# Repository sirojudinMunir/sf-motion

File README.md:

# SF-Motion

**Open-source BLDC/PMSM motor control platform based on STM32 and Field-Oriented Control (FOC).**

The project includes:

- FOC firmware
- Custom motor driver hardware
- KiCad schematic and PCB design
- Gerber and BOM files
- Python communication and control tools
- PyQt/PyQtGraph GUI for motor monitoring and testing

> ⚠️ This project is under active development. Hardware and firmware may change between versions.

## Hardware Prerequisites

You will need:
- FOC Driver Board
- ST-Link programmer/debugger with 3-pin Molex pico-blade P1.25mm connector
- DC power supply
- BLDC/PMSM motor
- diametrical magnet
- USB type-C cable
- power cable with XT-30 female connector

The hardware design is available in:
```
Hardware/
├── production/        # Gerber manufacturing files
├── .kicad_sch         # Schematic
├── .kicad_pcb         # PCB design
└── ...
```

## Software Prerequisites

### 1. STM32CubeMX

Used to configure the STM32 peripherals and generate the initial project configuration.

Download: https://www.st.com/en/development-tools/stm32cubemx.html

### 2. Visual Studio Code

Used as the main development environment.

Download: https://code.visualstudio.com/

### 3. PlatformIO

PlatformIO is used to build and upload the firmware.

Install PlatformIO through the VS Code extension:
1. Open VS Code.
2. Open Extensions.
3. Search for PlatformIO IDE.
4. Install the extension.
5. Restart VS Code if required.

Verify the installation:
``` bash
pio --version
```

If `pio` is not recognized in the terminal, use the PlatformIO terminal inside VS Code or add the PlatformIO CLI directory to your system PATH.

### 4. Python

Python is required for the communication tools and GUI.

Recommended version:
```text
Python 3.10+
```

Download: https://www.python.org/downloads/

Check the installation:
``` bash
python --version
```

Create a virtual environment (recommended):
``` bash
python -m venv .venv
```

Activate it on Windows:
``` bash
.venv\Scripts\activate
```

Activate it on Linux/macOS:
``` bash
source .venv/bin/activate
```

Install the required packages:
``` bash
pip install numpy pyserial PyQt5 pyqtgraph
```

## Getting Started

Clone the repository using Git:
``` bash
git clone https://github.com/sirojudinMunir/sf-motion.git
```

Enter the project directory:
``` bash
cd SF-Motion
```

## Building the Firmware

Open the project in VS Code with PlatformIO installed.

Build the firmware:
``` bash
pio run
```

If the build is successful, the firmware binary will be generated by PlatformIO.

## Upload Firmware

Connect the ST-Link to the FOC Driver board using the 3-pin PicoBlade connector.

The board can be powered from a **6–24 V external power supply**. For the initial test, it is recommended to use **USB Type-C** as the power source if applicable.

Upload the firmware:
``` bash
pio run -t upload
```

You can also use the Upload button in the PlatformIO interface in VS Code.

## For the first test

After uploading the firmware, follow these steps:

1. Make sure the D3 LED is blinking after the firmware starts.
2. Connect the BLDC/PMSM motor wires to the FOC Driver board. Make sure the diametrical magnet is securely mounted on the motor shaft and properly aligned with the magnetic encoder on the FOC Driver board. The board should be positioned directly beneath the magnet.
3. If you are using an external power supply, set the current limit to 1 A for the initial test. This helps prevent damage if there is an unexpected issue with the board or motor.
4. Connect the USB Type-C cable to the board.
5. Run the Python motor control program:
    ```python
    python communication/motor.py
    ```
6. Select the correct COM port and click Connect.

7. Before running the motor, set the correct motor pole pairs:
    ``` python
    motor.set_pole_pairs(<your_motor_pole_pairs>)
    ```
    Replace <your_motor_pole_pairs> with the actual number of pole pairs of your motor.
8. Run the self-commissioning process:
    ``` python
    motor.self_commissioning()
    ```
    The self-commissioning process measures the motor resistance and inductance and calibrates the magnetic encoder.
    >Important: During encoder calibration, make sure the motor rotates counter-clockwise (CCW). If the motor rotates in the opposite direction, swap any two motor wires to reverse the rotation.
    Automatic motor direction detection will be implemented in a future version.
9. Save configuration
    ``` python
    motor.set_save_config()
    ```
10. Test the FOC motor modes using:
    ``` python
    motor.set_motor_mode(<mode>)
    ```
    Available modes:

    0 -> for current control mode  
    1 -> for speed control mode  
    2 -> for position control mode  
    5 -> for open-loop mode  
    6 -> for disable the motor

> ⚠️ Keep the power supply current limit low during the first test. Do not increase the voltage or current limit until the board, encoder, and motor are confirmed to be working correctly.

---

## Support SF-Motion

If you find this project useful and would like to support its development,
you can become a sponsor:

Your support helps fund hardware development, testing, documentation,
and future improvements to SF-Motion.

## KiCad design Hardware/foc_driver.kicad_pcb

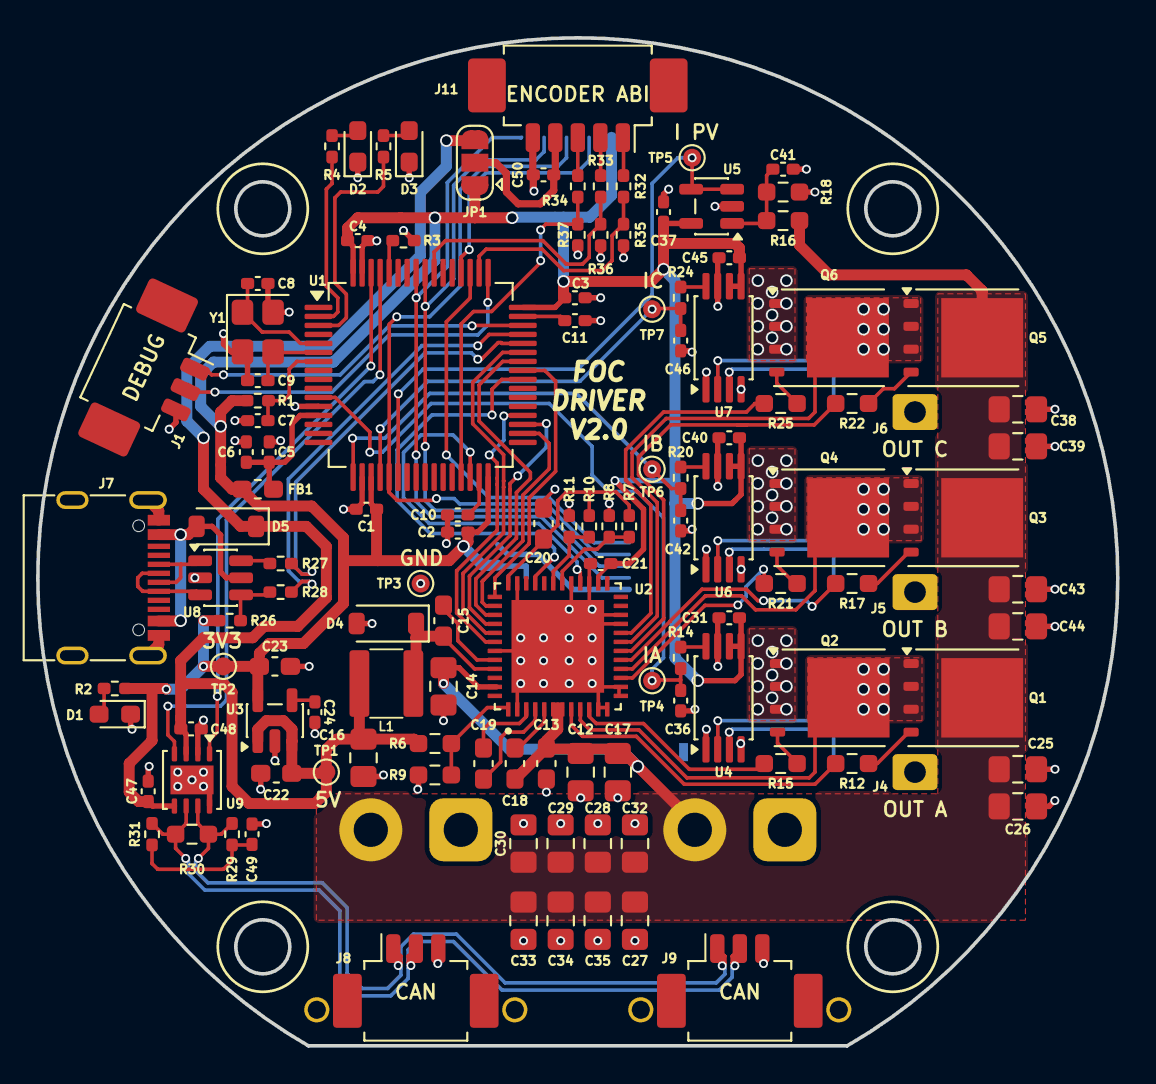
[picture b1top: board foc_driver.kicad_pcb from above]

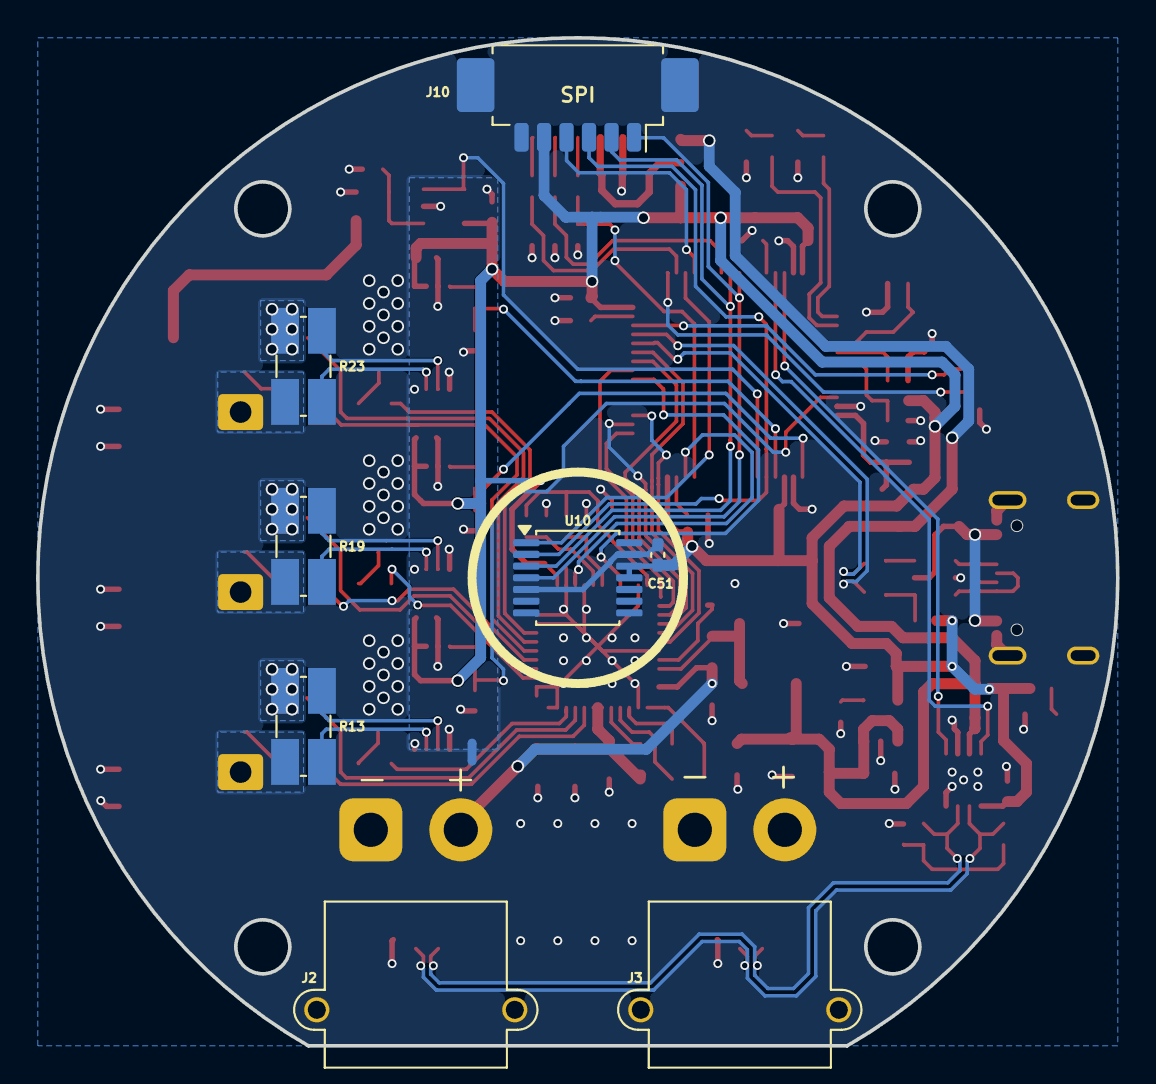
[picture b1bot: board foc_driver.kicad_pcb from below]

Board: 2 copper layers, 60.0 x 56.0 mm, 132 parts (9 on the bottom side), 93 nets.

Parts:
C1, C2, C3, C4, C5, C7, C10, C11, C21, C31, C37, C40, C41, C45, C47, C48, C49, C50, C51: 100nF; C_0402_1005Metric_Pad0.74x0.62mm_HandSolder
C6: 1uF; C_0402_1005Metric_Pad0.74x0.62mm_HandSolder
C8, C9: 33pF; C_0402_1005Metric_Pad0.74x0.62mm_HandSolder
C12, C16, C17, C25, C26, C27, C28, C29, C30, C32, C33, C34, C35, C38, C39, C43, C44: 10uF; C_0805_2012Metric_Pad1.18x1.45mm_HandSolder
C13, C15: 0.1uF; C_0603_1608Metric_Pad1.08x0.95mm_HandSolder
C14: 4.7uF; C_0805_2012Metric_Pad1.18x1.45mm_HandSolder
C18, C20, C22: 1uF; C_0603_1608Metric_Pad1.08x0.95mm_HandSolder
C19: 47nF; C_0603_1608Metric_Pad1.08x0.95mm_HandSolder
C23: 2.2uF; C_0603_1608Metric_Pad1.08x0.95mm_HandSolder
C24: 10nF; C_0402_1005Metric_Pad0.74x0.62mm_HandSolder
C36, C42, C46: 1nF; C_0402_1005Metric_Pad0.74x0.62mm_HandSolder
D1, D2: LED RED; LED_0603_1608Metric_Pad1.05x0.95mm_HandSolder
D3: LED GREEN; LED_0603_1608Metric_Pad1.05x0.95mm_HandSolder
D4, D5: MBR0530; D_SOD-123
FB1: fcm 1608-0603; L_0603_1608Metric_Pad1.05x0.95mm_HandSolder
J1, J8, J9: Conn_01x03_MountingPin; Molex_PicoBlade_53261-0371_1x03-1MP_P1.25mm_Horizontal
J2, J3: Conn_01x02; AMASS_XT30PW-M_1x02_P2.50mm_Horizontal
J4, J5, J6: Conn_01x01; SolderWire-0.25sqmm_1x01_D0.65mm_OD2mm
J7: USB_C_Receptacle_USB2.0_16P; USB_C_Receptacle_G-Switch_GT-USB-7010ASV
J10: Conn_01x06_MountingPin; Molex_PicoBlade_53261-0671_1x06-1MP_P1.25mm_Horizontal
J11: Conn_01x05_MountingPin; Molex_PicoBlade_53261-0571_1x05-1MP_P1.25mm_Horizontal
JP1: SolderJumper_3_Open; SolderJumper-3_P1.3mm_Open_RoundedPad1.0x1.5mm
L1: 22uH; L_SMD_4X4
NT1: NetTie_2; NetTie-2_SMD_Pad0.5mm
Q1, Q2, Q3, Q4, Q5, Q6: WSD30100DN56; TDSON-8-1
R1, R3: 10k; R_0402_1005Metric_Pad0.72x0.64mm_HandSolder
R2, R4, R5, R14, R20, R24, R32, R33, R34: 1k; R_0402_1005Metric_Pad0.72x0.64mm_HandSolder
R6: 18k; R_0603_1608Metric_Pad0.98x0.95mm_HandSolder
R7, R8, R10, R11: R; R_0402_1005Metric_Pad0.72x0.64mm_HandSolder
R9: 3k3; R_0603_1608Metric_Pad0.98x0.95mm_HandSolder
R12, R15, R17, R21, R22, R25: 10R; R_0603_1608Metric_Pad0.98x0.95mm_HandSolder
R13, R19, R23: 0.01R; R_Shunt_Ohmite_LVK20
R16: 39k; R_0603_1608Metric_Pad0.98x0.95mm_HandSolder
R18: 2k2; R_0603_1608Metric_Pad0.98x0.95mm_HandSolder
R26: 1k8; R_0402_1005Metric_Pad0.72x0.64mm_HandSolder
R27, R28: 100R; R_0402_1005Metric_Pad0.72x0.64mm_HandSolder
R29, R31: 30R; R_0402_1005Metric_Pad0.72x0.64mm_HandSolder
R30: 120R; R_0603_1608Metric_Pad0.98x0.95mm_HandSolder
R35, R36, R37: 2k; R_0402_1005Metric_Pad0.72x0.64mm_HandSolder
TP1, TP2, TP3, TP4, TP5, TP6, TP7: TestPoint; TestPoint_Pad_D1.0mm
U1: STM32F405RGTx; LQFP-64_10x10mm_P0.5mm
U2: DRV8323RHRGZR; QFN50P700X700X100-49N
U3: LP2985-3.3; SOT-23-5
U4, U6, U7: INA240A1PW; TSSOP-8_4.4x3mm_P0.65mm
U5: LM321; SOT-23-5
U8: USBLC6-2SC6; SOT-23-6
U9: TJA1051TK-3; HVSON-8-1EP_3x3mm_P0.65mm_EP1.6x2.4mm
U10: AS5047D; TSSOP-14_4.4x5mm_P0.65mm
Y1: 12MHz; Crystal_SMD_3225-4Pin_3.2x2.5mm

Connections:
+3V3: C1.1, C2.1, C3.1, C4.1, C21.2, C23.1, C31.1, C37.1, C40.1, C45.1, C47.2, C51.1, FB1.2, J10.5, JP1.1 (A), R1.1, R2.1, R26.1, TP2.1 (1_1), U1.19 (VDD), U1.32 (VDD), U1.48 (VDD), U1.64 (VDD), U2.26 (VREF), U3.5 (VOUT), U4.5 (V+), U4.6 (REF2), U5.5 (V+), U6.5 (V+), U6.6 (REF2), U7.5 (V+), U7.6 (REF2), U9.5 (VIO), U10.11 (VDD), U10.12 (VDD3V3)
+3V3A: C5.1, C6.1, FB1.1, U1.13 (VDDA)
+5V: C16.1, C22.1, C48.2, D5.1 (K), JP1.3 (B), L1.2, R6.1, TP1.1 (1_1), U3.1 (VIN), U3.3 (ON/~OFF), U9.3 (VCC)
/Communications/CAN_N: J8.2, J9.2, R30.2, R31.2, U9.6 (CANL)
/Communications/CAN_P: J8.1, J9.1, R29.2, R30.1, U9.7 (CANH)
/Communications/CAN_RX: U1.61 (PB8), U9.4 (RXD)
/Communications/CAN_TX: U1.62 (PB9), U9.1 (TXD)
/Communications/USB_N: R27.2, U1.44 (PA11)
/Communications/USB_P: R28.2, U1.45 (PA12)
/Communications/VBUS: D5.2 (A), J7.A4 (VBUS), J7.A9 (VBUS), J7.B4 (VBUS), J7.B9 (VBUS), U8.5 (VBUS)
/Encoders/CS0: U1.51 (PC10), U10.1 (~CS)
/Encoders/CS1: J10.4, U1.52 (PC11)
/Encoders/EXT_ENCDA: R32.1, R35.1, U1.50 (PA15)
/Encoders/EXT_ENCDB: R33.1, R36.1, U1.55 (PB3)
/Encoders/EXT_ENCDI: R34.1, R37.1, U1.29 (PB10)
/Encoders/MISO: J10.2, U1.56 (PB4), U10.3 (MISO)
/Encoders/MOSI: J10.1, U1.57 (PB5), U10.4 (MOSI)
/Encoders/SCK: J10.3, U1.21 (PA5), U10.2 (CLK)
/Gate Driver/EN_GATE: U1.40 (PC9), U2.33 (ENABLE)
/Gate Driver/FAULT: U1.30 (PB11), U2.28 (NFAULT)
/Gate Driver/GHA: R12.1, U2.8 (GHA)
/Gate Driver/GHB: R17.1, U2.17 (GHB)
/Gate Driver/GHC: R22.1, U2.18 (GHC)
/Gate Driver/GLA: R15.1, U2.10 (GLA)
/Gate Driver/GLB: R21.1, U2.15 (GLB)
/Gate Driver/GLC: R25.1, U2.20 (GLC)
/Gate Driver/IDRIVE: R7.2, R8.2, U2.30 (IDRIVE)
/Gate Driver/INH_A: U1.41 (PA8), U2.37 (INHA)
/Gate Driver/INH_B: U1.42 (PA9), U2.39 (INHB)
/Gate Driver/INH_C: U1.43 (PA10), U2.41 (INHC)
/Gate Driver/INL_A: U1.34 (PB13), U2.38 (INLA)
/Gate Driver/INL_B: U1.35 (PB14), U2.40 (INLB)
/Gate Driver/INL_C: U1.36 (PB15), U2.42 (INLC)
/Gate Driver/SHA: Q1.1 (S), Q1.2 (S), Q1.3 (S), Q2.5 (D), R13.1, U2.9 (SHA)
/Gate Driver/SHB: Q3.1 (S), Q3.2 (S), Q3.3 (S), Q4.5 (D), R19.1, U2.16 (SHB)
/Gate Driver/SHC: Q5.1 (S), Q5.2 (S), Q5.3 (S), Q6.5 (D), R23.1, U2.19 (SHC)
/Gate Driver/VDS: R10.2, R11.2, U2.31 (VDS)
/Inverter/ISENSE_A: C36.1, R14.2, TP4.1 (1_1), U1.11 (PC3)
/Inverter/ISENSE_B: C42.1, R20.2, TP6.1 (1_1), U1.17 (PA3)
/Inverter/ISENSE_C: C46.1, R24.2, TP7.1 (1_1), U1.20 (PA4)
/Inverter/OUT_A: J4.1 (Pin_1_1), R13.4
/Inverter/OUT_B: J5.1 (Pin_1_1), R19.4
/Inverter/OUT_C: J6.1 (Pin_1_1), R23.4
/Inverter/PV_SENSE: TP5.1 (1_1), U1.22 (PA6), U5.3 (-), U5.4
/MCU/BOOT0: R3.2, U1.60 (BOOT0)
/MCU/LED_G: R5.1, U1.3 (PC14)
/MCU/LED_R: R4.1, U1.2 (PC13)
/MCU/NRST: C7.1, R1.2, U1.7 (NRST)
/MCU/OSC_IN: C8.2, U1.5 (PH0), Y1.1
/MCU/OSC_OUT: C9.2, U1.6 (PH1), Y1.3
/MCU/SWCLK: J1.2, U1.49 (PA14)
/MCU/SWDIO: J1.1, U1.46 (PA13)
DVDD: C20.1, R7.1, R10.1, U2.36 (DVDD)
GND: C1.2, C2.2, C3.2, C4.2, C5.2, C6.2, C7.2, C8.1, C9.1, C10.2, C11.2, C12.2, C13.2, C14.2, C16.2, C17.2, C20.2, C21.1, C22.2, C23.2, C24.2, C25.1, C26.1, C27.1, C28.1, C29.1, C30.1, C32.1, C33.1, C34.1, C35.1, C38.1, C39.1, C41.2, C43.1, C44.1, C47.1, C48.1, C49.1, C50.1, C51.2, D1.1 (K), D2.1 (K), D3.1 (K), D4.2 (A), J1.3, J2.1, J3.1, J7.A1 (GND), J7.A12 (GND), J7.B1 (GND), J7.B12 (GND), J7.S1 (SHIELD), J8.3, J9.3, J10.6, J11.5, NT1.2, Q2.1 (S), Q2.2 (S), Q2.3 (S), Q4.1 (S), Q4.2 (S), Q4.3 (S), Q6.1 (S), Q6.2 (S), Q6.3 (S), R3.1, R8.1, R9.2, R11.1, R18.2, R35.2, R36.2, R37.2, TP3.1 (1_1), U1.12 (VSSA), U1.18 (VSS), U1.63 (VSS), U2.2 (PGND), U2.11 (SPA), U2.12 (SNA), U2.13 (SNB), U2.14 (SPB), U2.21 (SPC), U2.22 (SNC), U2.27 (DGND), U2.29 (MODE), U2.35 (AGND), U2.43 (BGND), U2.49 (EP), U3.2 (GND), U8.2 (GND), U9.2 (GND), U9.8 (S), U9.9 (GND), U10.5 (TST), U10.13 (GND), Y1.2 (G), Y1.4 (G)
GNDA: C31.2, C36.2, C37.2, C40.2, C42.2, C45.2, C46.2, NT1.1, U4.1 (GND), U4.4 (GND), U4.7 (REF1), U5.2 (V-), U6.1 (GND), U6.4 (GND), U6.7 (REF1), U7.1 (GND), U7.4 (GND), U7.7 (REF1)
unnamed: C49.2, R29.1, R31.1
unnamed: D1.2 (A), R2.2
unnamed: D2.2 (A), R4.2
unnamed: D3.2 (A), R5.2
unnamed: C15.2, D4.1 (K), L1.1, U2.45 (SW)
unnamed: J7.A6 (D+), J7.B6 (D+), U8.3 (I/O2)
unnamed: J7.A7 (D-), J7.B7 (D-), U8.1 (I/O1)
unnamed: J11.1, R32.2
unnamed: J11.2, R33.2
unnamed: J11.3, R34.2
unnamed: C50.2, J11.4, JP1.2 (C)
unnamed: Q1.4 (G), R12.2
unnamed: Q2.4 (G), R15.2
unnamed: Q3.4 (G), R17.2
unnamed: Q4.4 (G), R21.2
unnamed: Q5.4 (G), R22.2
unnamed: Q6.4 (G), R25.2
unnamed: R14.1, U4.8
unnamed: R20.1, U6.8
unnamed: R24.1, U7.8
unnamed: R26.2, R28.1, U8.4 (I/O2)
unnamed: R27.1, U8.6 (I/O1)
unnamed: C10.1, U1.31 (VCAP_1)
unnamed: C11.1, U1.47 (VCAP_2)
unnamed: C15.1, U2.44 (CB)
unnamed: C19.2, U2.4 (CPH)
unnamed: C19.1, U2.3 (CPL)
unnamed: R6.2, R9.1, U2.1 (FB)
unnamed: C18.1, U2.5 (VCP)
unnamed: C24.1, U3.4 (BP)
unnamed: R13.2, U4.2 (+)
unnamed: R13.3, U4.3 (-)
unnamed: C41.1, R16.2, R18.1, U5.1 (+)
unnamed: R19.2, U6.2 (+)
unnamed: R19.3, U6.3 (-)
unnamed: R23.2, U7.2 (+)
unnamed: R23.3, U7.3 (-)
VS: C12.1, C13.1, C14.1, C17.1, C18.2, C25.2, C26.2, C27.2, C28.2, C29.2, C30.2, C32.2, C33.2, C34.2, C35.2, C38.2, C39.2, C43.2, C44.2, J2.2, J3.2, Q1.5 (D), Q3.5 (D), Q5.5 (D), R16.1, U2.6 (VM), U2.7 (VDRAIN), U2.47 (VIN)

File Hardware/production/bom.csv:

Designator,Footprint,Quantity,Value,LCSC Part #
"C1, C10, C11, C2, C21, C3, C31, C37, C4, C40, C41, C45, C47, C48, C49, C5, C50, C51, C7",0402,19,100nF,C1525
"C12, C16, C17, C25, C26, C27, C28, C29, C30, C32, C33, C34, C35, C38, C39, C43, C44",0805,17,10uF,C22367830
"C13, C15",0603,2,0.1uF,C1591
C14,0805,1,4.7uF,C98192
"C18, C20, C22",0603,3,1uF,C5199872
C19,0603,1,47nF,C1622
C23,0603,1,2.2uF,C23630
C24,0402,1,10nF,C15195
"C36, C42, C46",0402,3,1nF,C14442
C6,0402,1,1uF,C29266
"C8, C9",0402,2,33pF,C70465
"D1, D2",0603,2,LED RED,C19171390
D3,0603,1,LED GREEN,C2986048
"D4, D5",D_SOD-123,2,MBR0530,C5204746
FB1,0603,1,fcm 1608-0603,C19330
"J1, J8, J9",Molex_PicoBlade_53261-0371_1x03-1MP_P1.25mm_Horizontal,3,Conn_01x03_MountingPin,C293630
J10,Molex_PicoBlade_53261-0671_1x06-1MP_P1.25mm_Horizontal,1,Conn_01x06_MountingPin,C17393620
J11,Molex_PicoBlade_53261-0571_1x05-1MP_P1.25mm_Horizontal,1,Conn_01x05_MountingPin,C17256390
"J2, J3",AMASS_XT30PW-M_1x02_P2.50mm_Horizontal,2,Conn_01x02,C431092
"J4, J5, J6",SolderWire-0.25sqmm_1x01_D0.65mm_OD2mm,3,Conn_01x01,
J7,USB_C_Receptacle_G-Switch_GT-USB-7010ASV,1,USB_C_Receptacle_USB2.0_16P,C2927039
L1,L_SMD_4X4,1,22uH,C6364792
"Q1, Q2, Q3, Q4, Q5, Q6",TDSON-8-1,6,WSD30100DN56,C2862136
"R1, R3",0402,2,10k,C60490
"R10, R11, R7, R8",0402,4,R,
"R12, R15, R17, R21, R22, R25",0603,6,10R,C844919
"R13, R19, R23",R_Shunt_Ohmite_LVK20,3,0.01R,C844898
"R14, R2, R20, R24, R32, R33, R34, R4, R5",0402,9,1k,C852624
R16,0603,1,39k,C163424
R18,0603,1,2k2,C125931
R26,0402,1,1k8,C163481
"R27, R28",0402,2,100R,C705627
"R29, R31",0402,2,30R,C852718
R30,0603,1,120R,C125925
"R35, R36, R37",0402,3,2k,C852711
R6,0603,1,18k,C309650
R9,0603,1,3k3,C144661
"TP1, TP2, TP3, TP4, TP5, TP6, TP7",TestPoint_Pad_D1.0mm,7,TestPoint,
U1,LQFP-64_10x10mm_P0.5mm,1,STM32F405RGTx,C15742
U10,TSSOP-14_4.4x5mm_P0.65mm,1,AS5047D,C2693743
U2,QFN50P700X700X100-49N,1,DRV8323RHRGZR,C543035
U3,SOT-23-5,1,LP2985-3.3,C95414
"U4, U6, U7",TSSOP-8_4.4x3mm_P0.65mm,3,INA240A1PW,C93965
U5,SOT-23-5,1,LM321,C5252901
U8,SOT-23-6,1,USBLC6-2SC6,C2827654
U9,HVSON-8-1EP_3x3mm_P0.65mm_EP1.6x2.4mm,1,TJA1051TK-3,C2875699
Y1,Crystal_SMD_3225-4Pin_3.2x2.5mm,1,12MHz,C9002

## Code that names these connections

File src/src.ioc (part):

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Mcu.Name=STM32F405RGTx
Mcu.Package=LQFP64
Mcu.UserName=STM32F405RGTx
PA10.Signal=S_TIM1_CH3
PA11.Mode=Device_Only
PA11.Signal=USB_OTG_FS_DM
PA12.Mode=Device_Only
PA12.Signal=USB_OTG_FS_DP
PA13.Mode=Serial_Wire
PA13.Signal=SYS_JTMS-SWDIO
PA14.Mode=Serial_Wire
PA14.Signal=SYS_JTCK-SWCLK
PA3.Signal=ADCx_IN3
PA4.Signal=ADCx_IN4
PA5.Mode=Full_Duplex_Master
PA5.Signal=SPI1_SCK
PA6.Signal=ADCx_IN6
PA8.Signal=S_TIM1_CH1
PA9.Signal=S_TIM1_CH2
PB11.GPIOParameters=GPIO_Label
PB11.GPIO_Label=NFAULT1
PB11.Signal=GPIO_Input
PB13.Mode=PWM Generation1 CH1 CH1N
PB13.Signal=TIM1_CH1N
PB14.Mode=PWM Generation2 CH2 CH2N
PB14.Signal=TIM1_CH2N
PB15.Mode=PWM Generation3 CH3 CH3N
PB15.Signal=TIM1_CH3N
PB4.Mode=Full_Duplex_Master
PB4.Signal=SPI1_MISO
PB5.Mode=Full_Duplex_Master
PB5.Signal=SPI1_MOSI
PB8.GPIOParameters=GPIO_PuPd
PB8.GPIO_PuPd=GPIO_PULLUP
PB8.Mode=CAN_Activate
PB8.Signal=CAN1_RX
PB9.Mode=CAN_Activate
PB9.Signal=CAN1_TX
PC10.GPIOParameters=GPIO_Label
PC10.GPIO_Label=SPI_CS
PC10.Signal=GPIO_Output
PC13-ANTI_TAMP.GPIOParameters=GPIO_Label
PC13-ANTI_TAMP.GPIO_Label=LED_R
PC13-ANTI_TAMP.Signal=GPIO_Output
PC14-OSC32_IN.GPIOParameters=GPIO_Label
PC14-OSC32_IN.GPIO_Label=LED_G
PC14-OSC32_IN.Signal=GPIO_Output
PC3.Signal=ADCx_IN13
PC9.GPIOParameters=GPIO_Label
PC9.GPIO_Label=EN_GATE1
PC9.Signal=GPIO_Output
PH0-OSC_IN.Mode=HSE-External-Oscillator
PH0-OSC_IN.Signal=RCC_OSC_IN
PH1-OSC_OUT.Mode=HSE-External-Oscillator
PH1-OSC_OUT.Signal=RCC_OSC_OUT
RCC.HSE_VALUE=12000000
RCC.SYSCLKFreq_VALUE=168000000
RCC.SYSCLKSource=RCC_SYSCLKSOURCE_PLLCLK
board=custom
